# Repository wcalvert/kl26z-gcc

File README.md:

A small development board for Kinetis KL26Z series ARM Cortex-M0 microcontrollers, plus gcc files to do some basic development. More to be added later.

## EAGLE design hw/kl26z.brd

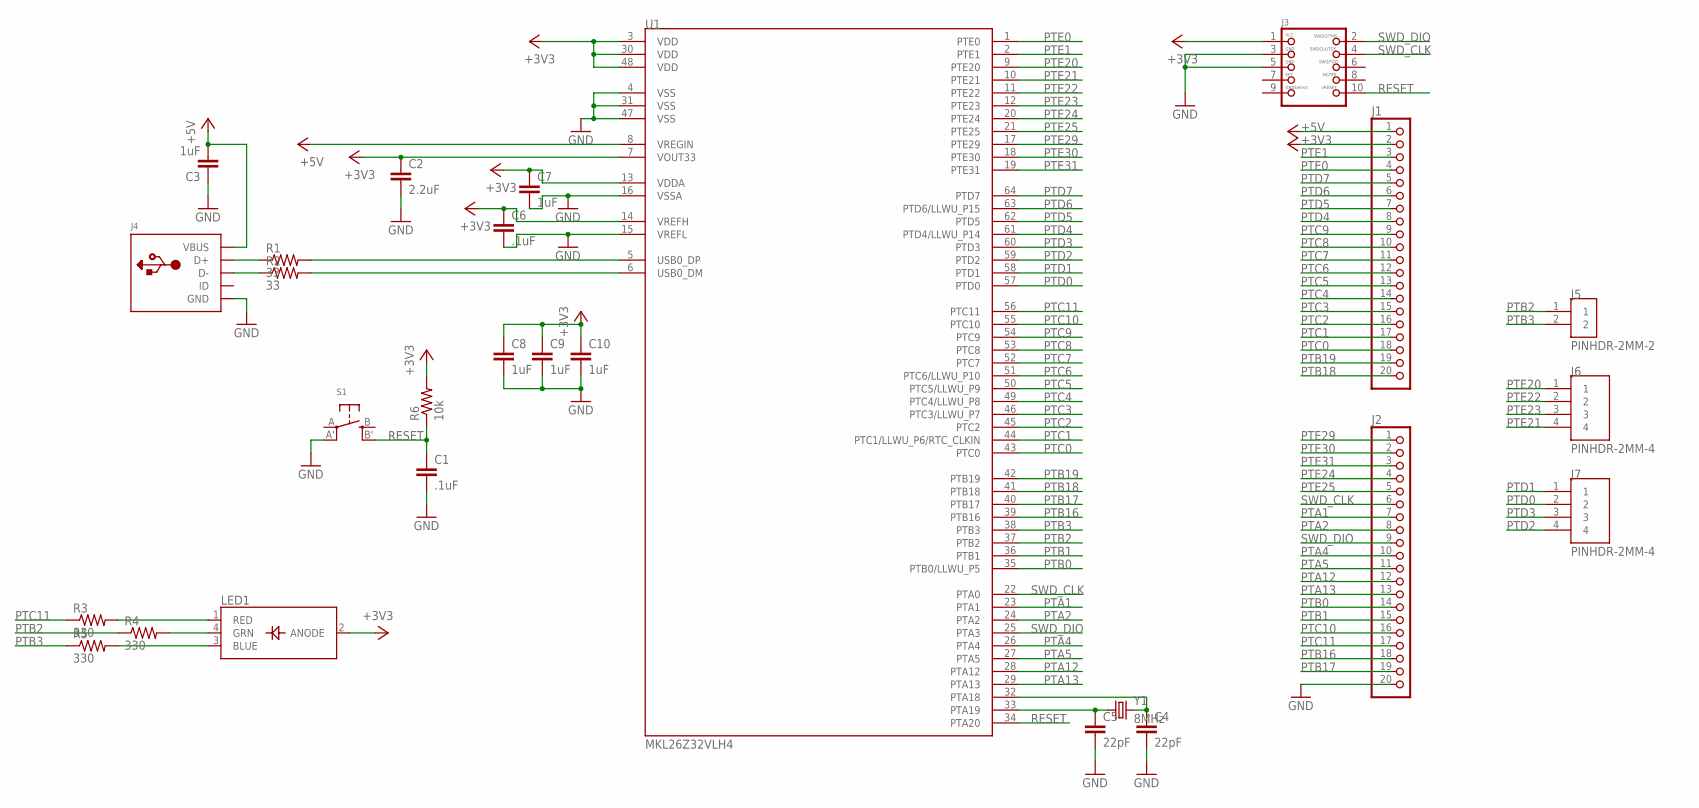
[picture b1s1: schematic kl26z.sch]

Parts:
C1, C6: .1uF; C0603
C2: 2.2uF; C0603
C3, C7, C8, C9, C10: 1uF; C0603
C4, C5: 22pF; C0603
J1, J2: HEADER-1X20ROUND; 1X20_ROUND
J3: JTAG-CORTEXM3; 2X05_1.27MM_SMT
J4: USBMINIB; USB-MINIB
J5: PINHDR-2MM-2
J6, J7: PINHDR-2MM-4
LED1: LED_RGB_PLCC4; RGBLED_PLCC4
R1, R2: 33; R0603
R3, R4, R5: 330; R0603
R6: 10k; R0603
S1: SWITCH_TACT_SMT4.6X2.8; BTN_KMR2_4.6X2.8
U1: MKL26Z32VLH4; LFQP64
Y1: 8MHz; CTS406

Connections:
+3V3: C2.1, C6.1, C7.1, C8.1, C9.1, C10.1, J1.2, J3.1, LED1.2 (ANODE), R6.2, U1.3 (VDD), U1.7 (VOUT33), U1.13 (VDDA), U1.14 (VREFH), U1.30 (VDD), U1.48 (VDD)
+5V: C3.2, J1.1, J4.VBUS, U1.8 (VREGIN)
GND: C1.2, C2.2, C3.1, C4.2, C5.2, C6.2, C7.2, C8.2, C9.2, C10.2, J2.20, J3.3, J3.5, J4.GND, S1.A' (P1), U1.4 (VSS), U1.15 (VREFL), U1.16 (VSSA), U1.31 (VSS), U1.47 (VSS)
unnamed: J4.D+, R1.1
unnamed: J4.D-, R2.1
unnamed: R1.2, U1.5 (USB0_DP)
unnamed: R2.2, U1.6 (USB0_DM)
unnamed: C5.1, U1.33 (PTA19), Y1.1
unnamed: C4.1, U1.32 (PTA18), Y1.3 (2)
unnamed: LED1.1 (RED), R3.2
unnamed: LED1.4 (GRN), R4.2
unnamed: LED1.3 (BLUE), R5.2
PTA1: J2.7, U1.23 (PTA1)
PTA2: J2.8, U1.24 (PTA2)
PTA4: J2.10, U1.26 (PTA4)
PTA5: J2.11, U1.27 (PTA5)
PTA12: J2.12, U1.28 (PTA12)
PTA13: J2.13, U1.29 (PTA13)
PTB0: J2.14, U1.35 (PTB0/LLWU_P5)
PTB1: J2.15, U1.36 (PTB1)
PTB2: J5.1, R4.1, U1.37 (PTB2)
PTB3: J5.2, R5.1, U1.38 (PTB3)
PTB16: J2.18, U1.39 (PTB16)
PTB17: J2.19, U1.40 (PTB17)
PTB18: J1.20, U1.41 (PTB18)
PTB19: J1.19, U1.42 (PTB19)
PTC0: J1.18, U1.43 (PTC0)
PTC1: J1.17, U1.44 (PTC1/LLWU_P6/RTC_CLKIN)
PTC2: J1.16, U1.45 (PTC2)
PTC3: J1.15, U1.46 (PTC3/LLWU_P7)
PTC4: J1.14, U1.49 (PTC4/LLWU_P8)
PTC5: J1.13, U1.50 (PTC5/LLWU_P9)
PTC6: J1.12, U1.51 (PTC6/LLWU_P10)
PTC7: J1.11, U1.52 (PTC7)
PTC8: J1.10, U1.53 (PTC8)
PTC9: J1.9, U1.54 (PTC9)
PTC10: J2.16, U1.55 (PTC10)
PTC11: J2.17, R3.1, U1.56 (PTC11)
PTD0: J7.2, U1.57 (PTD0)
PTD1: J7.1, U1.58 (PTD1)
PTD2: J7.4, U1.59 (PTD2)
PTD3: J7.3, U1.60 (PTD3)
PTD4: J1.8, U1.61 (PTD4/LLWU_P14)
PTD5: J1.7, U1.62 (PTD5)
PTD6: J1.6, U1.63 (PTD6/LLWU_P15)
PTD7: J1.5, U1.64 (PTD7)
PTE0: J1.4, U1.1 (PTE0)
PTE1: J1.3, U1.2 (PTE1)
PTE20: J6.1, U1.9 (PTE20)
PTE21: J6.4, U1.10 (PTE21)
PTE22: J6.2, U1.11 (PTE22)
PTE23: J6.3, U1.12 (PTE23)
PTE24: J2.4, U1.20 (PTE24)
PTE25: J2.5, U1.21 (PTE25)
PTE29: J2.1, U1.17 (PTE29)
PTE30: J2.2, U1.18 (PTE30)
PTE31: J2.3, U1.19 (PTE31)
RESET: C1.1, J3.10, R6.1, S1.B' (S1), U1.34 (PTA20)
SWD_CLK: J2.6, J3.4, U1.22 (PTA0)
SWD_DIO: J2.9, J3.2, U1.25 (PTA3)

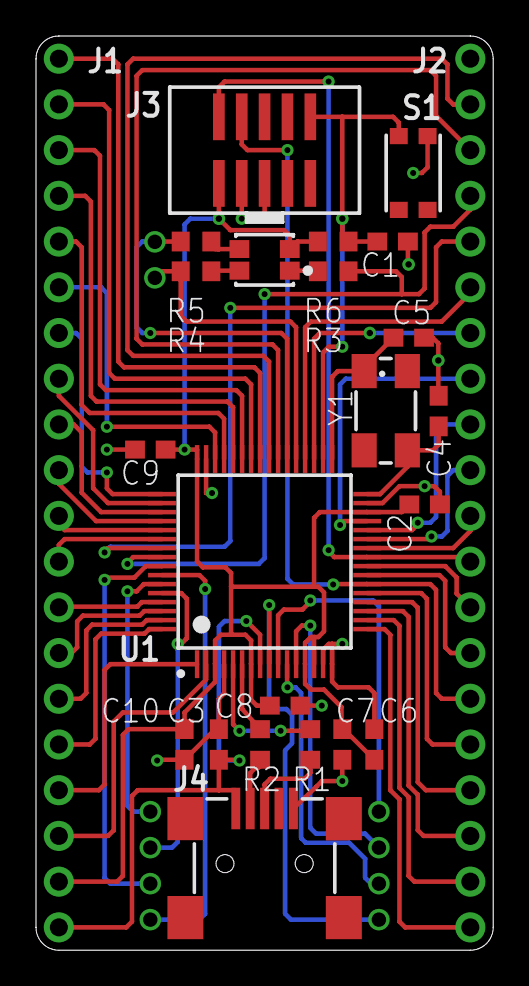
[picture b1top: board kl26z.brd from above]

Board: 2 copper layers, 25.4 x 50.8 mm, 27 parts (0 on the bottom side), 60 nets.

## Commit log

2014-06-25 Adding files

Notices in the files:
parts and their libraries:
microbuilder: This work is placed in the public domain, and may be freely used for commercial and non-commercial work with the following conditions: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
